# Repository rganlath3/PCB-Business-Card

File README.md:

# PCB Business Card

<!-- ABOUT -->
## About The Project
A business card with embedded IPS display, SMD pushbuttons, and a XIAO nRF5240 Sense designed to run off a slim LiPo Battery.
The goal of this PCB is to create an artistic business card for conventions, maker spaces, and other social events that stands out either assembled or unassembled for portability.

<!-- REQUIREMENTS -->
### Design Tools & Requirements

#### Software Requirements
- VS Code / Arduino (Programming IDE)
- Autodesk Fusion360 (Free CAD Software)
- KiCAD 9.0 (Open Source PCB Design Software)
- Ultimaker Cura (Free 3D Slicing Software)
- QR Code Generator

#### Bill of Materials
- Custom PCBs
- MCU: XIAO nRF5240 Sense
- Low Profile SMD Momentary Pushbutton: TL3342
- LIPO Connector
- LIPO Battery
- 1.14" 135x240 RGB IPS LCD SPI Display with ST7789V driver IC.

<!-- POWER -->
### Component Power Draw
- XIAO nRF5240 Sense:
- IPS Display:
- Total:
- With Safety Factor (x1.25):
- Recommended Lipo: 
- Estimated Battery Life:

<!-- PCB Design -->
### PCB Design

This PCB is used to interface a XIAO nRF5240 Sense with the following components:
- SMD Pushbuttons
- IPS Display
- Power Source (Lipo Battery)

I did some research on artistic designs and found people using soldermask as a visual aesthetic. When the board is finished with ENIG, it produces a protected and nice gold finish.
For the board thickness I went with 0.8mm. (Typical board is 1.6mm). For future revisions, I may make the board even thinner.
The end goal is not use a breakout board and to simply have the nRF5240 or another board like the ESP32-S3 bare chip used along with battery charging and microphone circuits to reduce the physical space taken up. 

<!-- Software -->
### Software Design
With 4x buttons available along with a microphone input, a variety of things can be displayed on the screen.
I wanted to incorporate a menu system so I can toggle between different modes such as a battery readout display, static image display such as for a QR code, a looping GIF display, a sound reactive display mode, and a control mode to set ambient audio input levels. The limitation of all of this is the amount of flash memory on the XIAO nRF5240. For future revisions, I can incorporate a microSD card.

#### Menu Display
- Call
    - Snake
    - Campbell
    - Naomi
    - Miller
    - Liquid
    - Otacon
    - Sniper Wolf
    - Meryl
    - Mei Ling
    - Nastasha
    - Dt
- Incoming Call
- Animated
    - Snake
    - Campbell
    - Naomi
    - Miller
    - Otacon
    - Sniper Wolf
    - Meryl
    - Mei Ling
    - Nastasha
- Settings
    - Brightness
    - Restart System
- QR
    - QR code for this project
    - QR code for my LinkedIn
    - QR code for my github
- Games
    - TBD
- Sleep

#### Battery Readout Display
TBD

#### Static Image Display
TBD

#### Looping GIF Display
TBD

#### Sound Reactive Display
TBD

#### Ambient Audio Config Display
TBD

#### Game Display
TBD

<!-- CONTRIBUTING -->
## Contributing & Donations

Any donation helps to support parts for future open source projects!
[Buy Me a Coffee ☕](https://www.buymeacoffee.com/rganlath)

Contributions are what make the open source community such an amazing place to learn, inspire, and create. Any contributions you make are **greatly appreciated**.

If you have a suggestion that would make this better, please fork the repo and create a pull request. You can also simply open an issue with the tag "enhancement".
Don't forget to give the project a star! Thanks again!

<!-- LICENSE -->
## License
The contents of this project itself is licensed under CERN-OHL-S-2.0 and the underlying source code is licensed under GNU GPLv3. Both of these licenses require attribution.

<!-- SPECIAL THANKS -->
## Special Thanks
Special thanks to the following creators' github repos for inspiration and techniques used in this project:
- River Wang: https://github.com/urfdvw/cardtuber
- Anythony Kouttron: https://salvagedcircuitry.com/pcb-business-card.html

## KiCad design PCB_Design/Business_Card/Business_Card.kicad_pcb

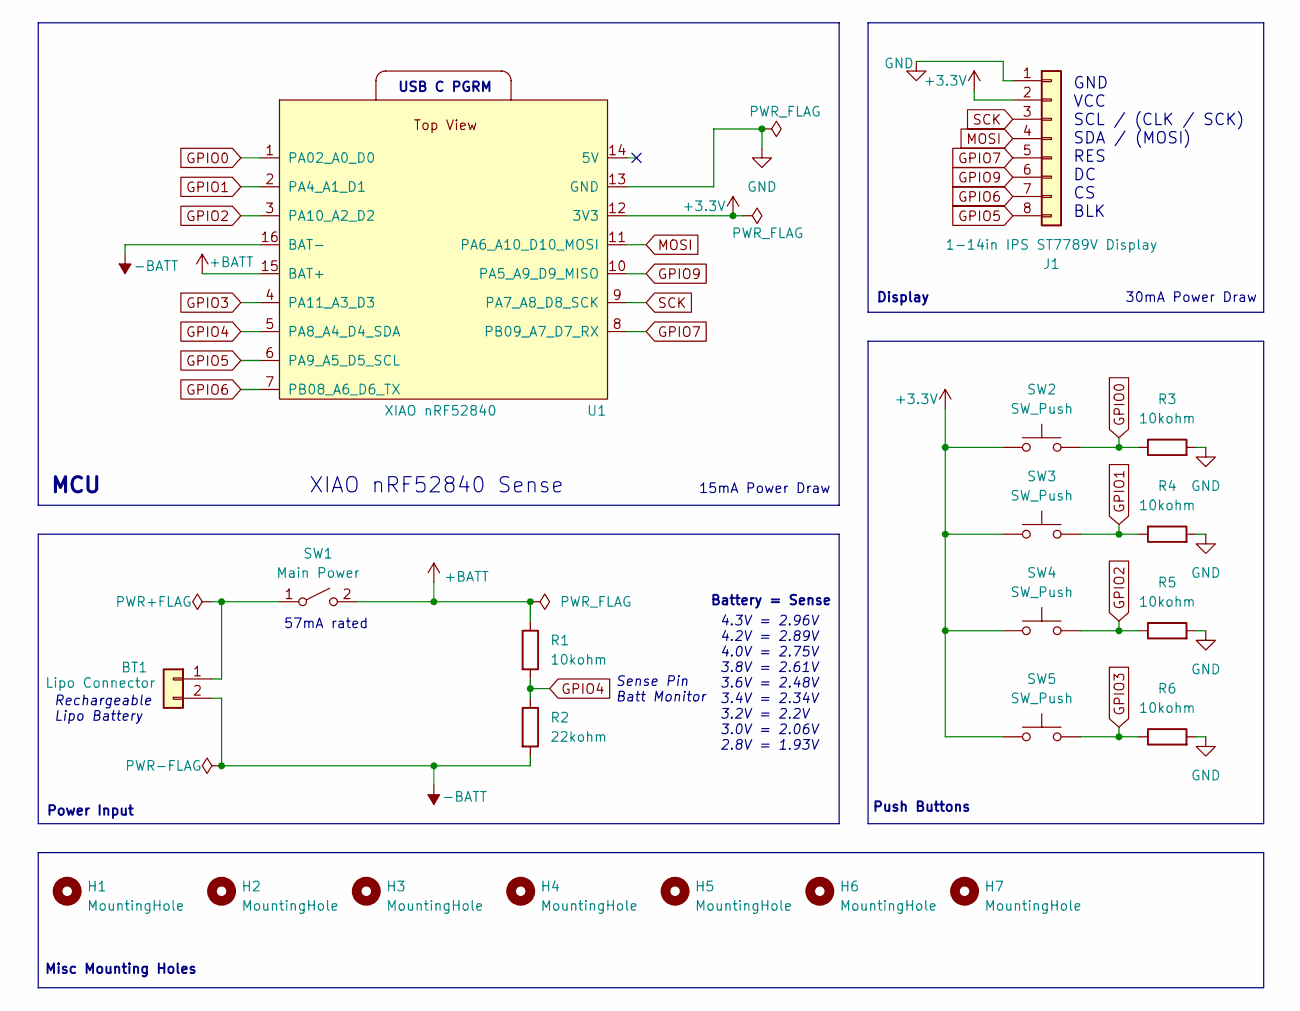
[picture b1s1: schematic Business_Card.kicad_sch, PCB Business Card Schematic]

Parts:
BT1: Lipo Connector; PinHeader_2x01_P2.00mm_Vertical_SMD
H1, H2, H3, H4: MountingHole; MountingHole_2.5mm_Pad_TopOnly
H5, H7: MountingHole; MountingHole_3.7mm_Core
H6: MountingHole; MountingHole_3.7mm_Lanyard_Core
J1: 1-14in IPS ST7789V Display; 1-14in_IPS_ST7789V_Display
R1, R3, R4, R5, R6: 10kohm; R_1206_3216Metric_Pad1.30x1.75mm_HandSolder
R2: 22kohm; R_1206_3216Metric_Pad1.30x1.75mm_HandSolder
SW1: Main Power; PinHeader_2x01_P2.00mm_Vertical_SMD
SW2, SW3, SW4, SW5: SW_Push; SW_SPST_TL3342
U1: XIAO nRF52840; XIAO-nRF52840-SMD_Revised

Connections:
+3.3V: J1.2, SW2.1, SW3.1, SW4.1, SW5.1, U1.12 (3V3)
+BATT: R1.1, SW1.2 (B), U1.15 (BAT+)
-BATT: BT1.2, R2.2, U1.16 (BAT-)
GND: J1.1, R3.2, R4.2, R5.2, R6.2, U1.13 (GND)
GPIO0: R3.1, SW2.2, U1.1 (PA02_A0_D0)
GPIO1: R4.1, SW3.2, U1.2 (PA4_A1_D1)
GPIO2: R5.1, SW4.2, U1.3 (PA10_A2_D2)
GPIO3: R6.1, SW5.2, U1.4 (PA11_A3_D3)
GPIO4: R1.2, R2.1, U1.5 (PA8_A4_D4_SDA)
GPIO5: J1.8, U1.6 (PA9_A5_D5_SCL)
GPIO6: J1.7, U1.7 (PB08_A6_D6_TX)
GPIO7: J1.5, U1.8 (PB09_A7_D7_RX)
GPIO9: J1.6, U1.10 (PA5_A9_D9_MISO)
MOSI: J1.4, U1.11 (PA6_A10_D10_MOSI)
unnamed: BT1.1, SW1.1 (A)
SCK: J1.3, U1.9 (PA7_A8_D8_SCK)

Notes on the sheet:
MCU
Battery = Sense
Power Input
30mA Power Draw
57mA rated
Push Buttons
XIAO nRF52840 Sense
Misc Mounting Holes
Sense Pin Batt Monitor
GND VCC SCL / (CLK / SCK) SDA / (MOSI) RES DC CS BLK
15mA Power Draw
Rechargeable Lipo Battery
Display
USB C PGRM
4.3V = 2.96V 4.2V = 2.89V 4.0V = 2.75V 3.8V = 2.61V 3.6V = 2.48V 3.4V = 2.34V 3.2V = 2.2V 3.0V = 2.06V 2.8V = 1.93V

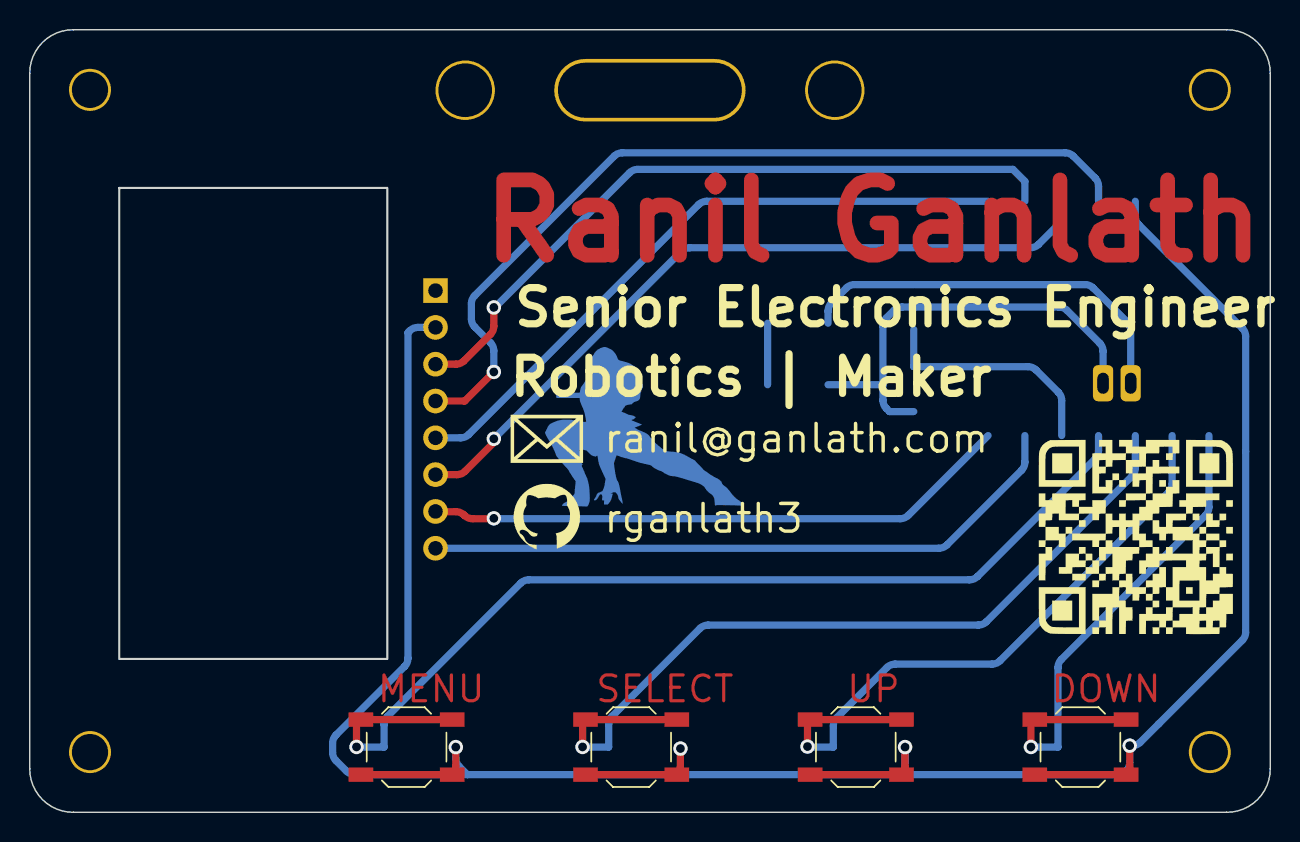
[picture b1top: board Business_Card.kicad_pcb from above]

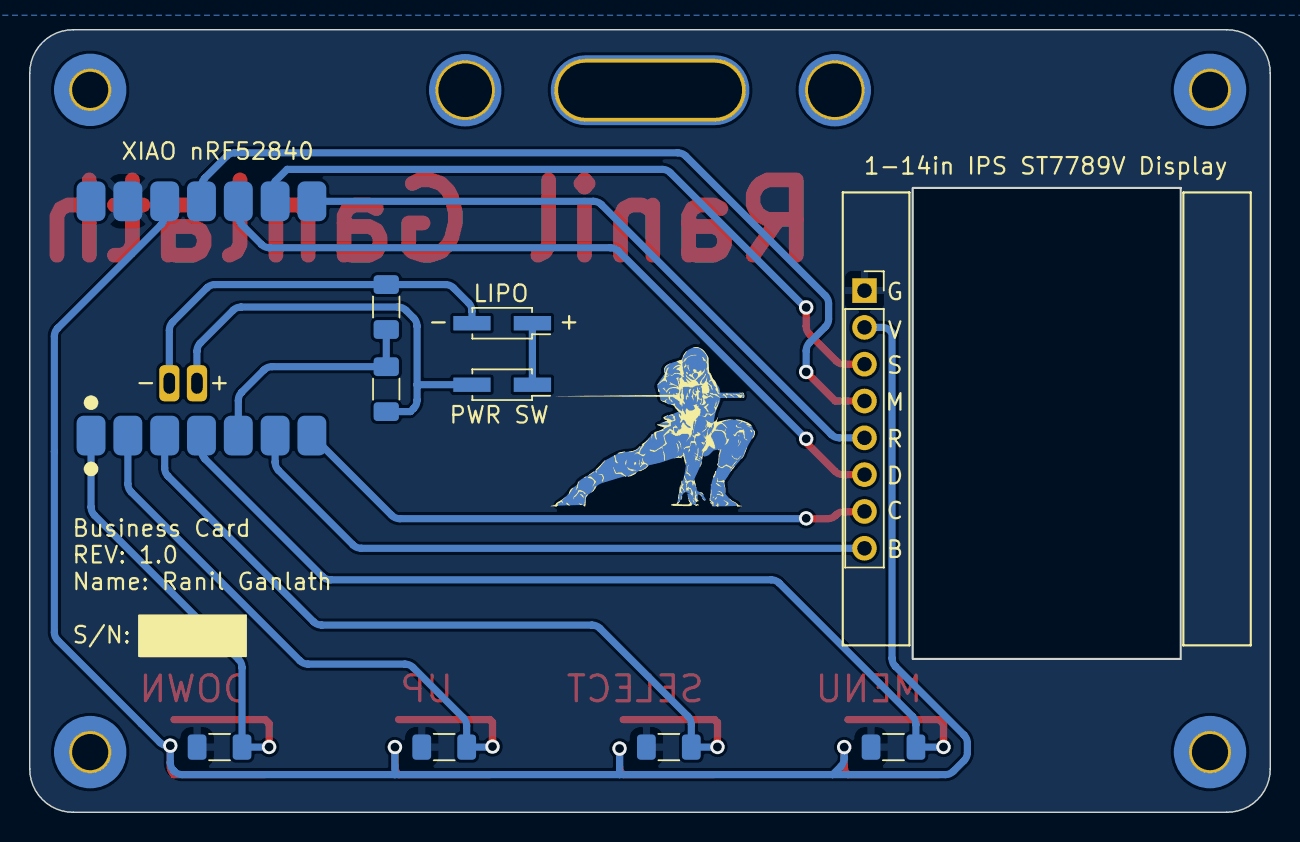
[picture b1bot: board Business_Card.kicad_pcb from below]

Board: 2 copper layers, 85.6 x 53.9 mm, 21 parts (13 on the bottom side), 16 nets.

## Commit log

2025-06-12 Initial Project Files
2025-06-13 PCB Schematic and Layout Updates
2025-06-18 Initial Testing Scripts created
2025-06-18 Initial Test Scripts created
2025-06-18 PCB Revisions
2025-06-18 Minor Fixes
2025-06-18 Added special thanks section
2025-07-10 Code migrated from XIAO Sense to ESP32-S3 board.
2025-07-17 Enclosure Updates
2025-07-17 Documentation Updates
2025-07-17 Core programming
    Rehauled code to work with ESP32-S3 XIAO compatible board

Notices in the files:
README.md:
Hardware License: CERN-OHL-S-2.0
Software License: GPL v3
